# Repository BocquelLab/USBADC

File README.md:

# USBADC
Le USBADC est un petit PCB qui implémente plusieurs fonctionnalités:
+ Lecture de la tension de sortie du power meter
+ Lecture de la température ambiante
+ Communication USB pour interfacer avec un ordinateur
+ Génération de 28 volts 1 ampère à partir de 12 volts 3 Ampères pour l'amplificateur RF
+ Génération de 5 volts pour le power meter
+ Contrôlle de la vitesse du ventilateur pour évacuer la chaleur
+ 6 sorties open-drain pour pouvoir controller des appareils nécessitant de la puissance (`PB1`, `PB3`, `PB4`, `PB5`, `PB6`, `PB7`)
+ 6 sorties digitales 3.3 volts pour du contrôlle ne nécessitant pas de puissance (`PA3`, `PA4`, `PA5`, `PA6`, `PA7`, `PA8`)
+ LED de statut du PCB, `D2` clignote lorsque le micro-contrôlleur n'a pas d'erreurs, et 4 autres LEDs indiquent si les générateurs de tensions fonctionnent (3.3V, 5V, 12V, 28V)

## Hardware
KiCad 10.0 a été utilisé pour la conception du schématique et du PCB.

### Composantes

1. Entré 12V 3A
2. Sortie 28V 1A
3. Boost 12V -> 28V
4. Buck 12V -> 5V
5. Régulateur 5V -> 3.3V
6. Microcontrôlleur STM32U073K8U6
7. Connecteur USB A femelle
8. Connecteur SWD (Single Wire Debug)
9. Sorties open-drain et low power
10. Sortie PWM pour fan
11. Sortie pour alimentation du powermeter et entrée de la température
12. Entrée pour lecture de la puissance RF

### Programmation
Pour envoyer un programme sur le micro-contrôlleur, il y a le port USB ainsi qu'un port SWD près du connecteur USB (header 6 pins).
Pour le flasher par USB, il faut utiliser le périphérique DFU (Download Firmware Upgrade) qu'expose le bootloader to STM32. Par contre, je ne sais pas pourquoi, je n'ai pas été capable de le faire fonctionner plus qu'une seule fois.

Pour le flasher par SWD, il faut un STlink. J'ai utilisé un [STlink-V3MINIE](https://www.st.com/en/development-tools/stlink-v3minie.html) auquel j'avais accès, il serait peut-être pertinent de s'en acheter un. J'ai aussi utilisé [stlink-tools](https://github.com/stlink-org/stlink) pour envoyer le programme. Il faut brancher:

| stlink | PCB   |
|:------:|:-----:|
| VCC    | VDD1  |
| CLK    | SWCLK |
| GND    | GND   |
| TMS    | SWDIO |
| RST    | NRST  |

Le pinout du PCB est visible sur KiCad, l'ordre est VCC, SWCLK, GND, SWDIO, NRST, no-connect en partant de la pin extérieure.

### USB
La communication USB est faites avec un `STM32U073K8U6`, un micro-contrôlleur peu coûteux. C'est le moins cher qui a toutes les fonctionnalitées voulues, l'horloge pour le USB est générée à l'interne du chip.

### Génération 28V et 5V
Les bucks et boosts ont été générées avec l'outil [WEBENCH](https://webench.ti.com/power-designer/switching-regulator?powerSupply=0) de Texas Instrument pour être sûr que les circuits fonctionnent, jusqu'à maintenant, il n'y a eu aucuns problèmes.

### Sécurité
Pour la génération du 28V, il y a ~28 watts qui transitent dans cette partie du circuit. Il y a une fuse 4 ampères `F2` à l'entrée 12V du circuit et une fuse 1.5 ampères `F1` à la sortie 28V. De plus, il y a une diode schottky à la sortie 28V pour éviter d'envoyer des pics de tensions à l'amplificateur. Il y a aussi des condensateurs de capacitance équivalente 110µF pour lisser la tension entrante dans l'amplificateur.

Il y a des points de tests un peu partout sur le PCB pour être capable de débugger plus facilement si il arrive un problème.

### Boutons
Le PCB possède deux boutons, `BOOT0` et `Reset`.

`Reset` permet de redémarrer le microcontrôlleur, pratique pour débugger ou pour le redémarrer si il ne répond pas.

`BOOT0` permet de signaler au bootloader du microcontrôlleur que l'on désire flasher un programme pour qu'il expose la classe `DFU`. Il faut simplement tenir le bouton en appuyant sur `Reset`. Comme mentionné plus tôt, je ne comprends pas pourquoi je n'arrive pas à faire fonctionner cette option.

### Corrections à apporter sur une version future
Les connecteurs pour le ventilateur et le power meter overlap et ne peuvent donc pas être soudés directement sur le PCB.

Trouver pourquoi la programmation par DFU ne fonctionne pas et régler le problème.

Il m'est arrivé une fois que le board ne voulait pas démarrer, j'ai trouvé qu'il s'exposait comme périphérique DFU au démarage au lieu de CDC ACM et je n'étais pas capable de le faire booter plus loin que le bootloader. Je l'ai reflashé et ça a fonctionné, je n'ai pas revu ça depuis.

Mettre un connecteur USB mâle à la place d'un connecteur USB femelle car les connecteurs femelles sont réservés aux hôtes USB et les mâles aux périphériques.

Monitorer la tension du 28V avec le STM32 pour pouvoir voir son statut par USB au lieu de devoir regarder la LED. Sur la version actuelle, il est possible de mettre un diviseur de tension sur le pad 28V et rentrer ça dans la pin A3.

## Firmware
La grande majorité du code dans `firmware/` a été générée avec `STM32CubeMX`, un outil pour initialiser des projets pour des STM32, ils s'occupent d'initialiser toutes les périphériques, vérifier que la configuration de clocks choisie est correcte, etc.

Les paramètres pour CubeMX sont dans le fichier `firmware/USBADC.ioc`.

Le coeur de la logique a été implémentée dans `firmware/USBX/App/` en C.

### Compilation
Pour compiler le programme, il suffit d'écrire `make` si la toolchain de développement `arm` est installée. Je développais sur un ordinateur Linux et je roulais souvant 
```
make -j4; st-flash erase; st-flash write build/USBADC.bin 0x08000000
```
pour compiler et puis envoyer le programme sur le microcontrôlleur. Je ne suis pas certain que les `Makefile` sont supportés dans `STM32CubeIDE` (IDE de développement pour un STM32 installée sur l'ordinateur du laboratoire).

J'ai utilisé la "Arm GNU Toolchain 15.2.Rel1 (Build arm-15.86)) 15.2.1 20251203". Tout fonctionne avec celle là, il n'y a surement pas de soucis à prendre une autre version.

### Débuggage
Pour débugger, `STM32CubeIDE` et `stlink-tools` permettent d'ouvrir une session `gdb` et d'explorer la mémoire du microcontrolleur. Avec `stlink-tools`, je roulais dans un terminal `st-util` et dans l'autre `gdb build/USBADC.elf`, puis dans la session gdb `target remote localhost:4242`.

### Connection USB
Le périphérique USB crée expose une classe USB CDC ACM, (Character Device Class, Abstract Control Modem). Cette classe permet d'envoyer une série d'octet à l'appareil ainsi que d'en recevoir une. Lorsque branchée dans un ordinateur, le PCB devrait apparaître comme `/dev/ttyUSB*` sur Linux et `COM*` sur Windows. La LED devrait aussi clignotée si le microcontrôlleur est alimentée correctement et qu'il n'y a pas d'erreurs.

### Protocole de communication
La communication se produit par paquets entre le serveur (l'ordinateur) et le client (l'USBADC).
Un packet est une liste d'octets qui représente une commande ou une réponse. Le préfixe `0x` dénote de l'hexadécimale.

| Bytes       | Name        | Type      | Description                              |
|-------------|-------------|-----------|------------------------------------------|
| `0-3`       | Magic       | `u8[4]`   | `0xAA` `0x55` `0xAA` `0x55`              |
| `4-5`       | ID          | `u16`     | Request/response identifier.             |
| `6`         | Type        | `u8`      | Message type.                            |
| `7`         | Data Length | `u8`      | Bytes following this field.              |
| `8..7+N`    | Data        | `u8[]`    | Type-specific payload.                   |
| `8+N..11+N` | CRC         | `u32`     | Packet checksum using CRC32.             |

Le champs `Magic` permet d'identifier le début d'un paquet. `0xAA55AA55` a été choisi car c'est une séquence qui a peu de chance d'arriver avec du bruit ou dans des données, aussi, en binaire, les bits de 0xAA et 0x55 alternent et ça permet de reconnaitre à l'oeil le début de la séquence.

Le champs `ID` permet à l'USBADC de spécifier à quel paquet il répond en spécifiant l'ID du message qu'il a reçu dans sa réponse. Cela permet de répondre aux paquets dans un ordre différent de celui dans lequel ils ont été reçues si besoin.

Le champs `Type` est le type du message (ping, read_adc, write_pin, reboot, ...) et permet de spécifier comment interpréter les données,

Le champs `Data Length` est la longeur du champs `Data` en octets

Le champs `Data` est les données associées au `Type` choisi.

Le champs `CRC` (Cyclical Redundancy Checksum) sert à vérifier l'intégrité des données reçues. Lors de la réception d'un paquet, on calcule le checksum de tous les octets précédents. Si le checksum est identique à celui reçue, on peut être confiant qu'il n'y a pas eu d'erreur de transmission.

Le protocole est ses fonctions de sérialisation/désérialisation sont spécifiées dans `firmware/USBX/App/protocol.h` et `firmware/USBX/App/protocol.c`.
Les structures qui représentent les données transmises ont l'attribut `__attribute__((packed))` pour éviter les champs de "padding". Cet attribute garanti qu'il n'y en aura pas.

Sur le message `REQUEST_PING`, le client répond avec le message `RESPONSE_PONG` avec les mêmes données. Cela permet de s'assurer que le client fonctionne correctement.

Sur le message `REQUEST_READ_ADC`, le client répond avec `RESPONSE_READ_ADC` la tension lue sur le channel correspondant.

Sur le mesasge `REQUEST_WRITE_PIN`, le client répond avec `RESPONSE_STATUS` et sort l'état demandée sur la pin demandée.

Sur le mesasge `REQUEST_REBOOT`, le client répond avec `RESPONSE_STATUS` et redémarre (la communication sera coupée).

Sur le message `REQUEST_VERSION`, le client répond avec la version du protocole qu'il utilise. Cela permet de s'assurer que le client et le serveur sont sur la même version et que toutes les fonctionnalitées sont fonctionelles et supportées des deux côtés.

Sur tous les messages, le client peut répondre avec `RESPONSE_STATUS` et spécifier la raison (`enum USBADC_PROTOCOL_RESPONS_STATUS_REASONS`).

### Fichiers (`firmware/USBX/App/`)
+ `app_usbx_device.c`: Point d'entrée `ThreadX` qui initialise les tâches et le périphérique USB et les files.
+ `ux_device_cdc_acm.c`: Définitions de toutes les tâches concurrentes qui roulent, dont l'écriture et la lecture sur le canal USB, la lecture de l'ADC et le contrôle de la vitesse du ventilateur.
+ `byte_vector.c`: Définition des fonctions pour manipuler une liste d'octets qui ne peut pas être agrandie.
+ `protocol.c`: Définition des fonctions pour sérialiser/désérialiser les packets envoyées/reçues

## Software
Python 3.11 a été utilisé.

Dans `software/USBADC.py`, il y a la classe `USBADC` qui permet de communiquer avec le périphérique. Il est nécessaire d'installer `pyserial` pour être capable de communiquer.

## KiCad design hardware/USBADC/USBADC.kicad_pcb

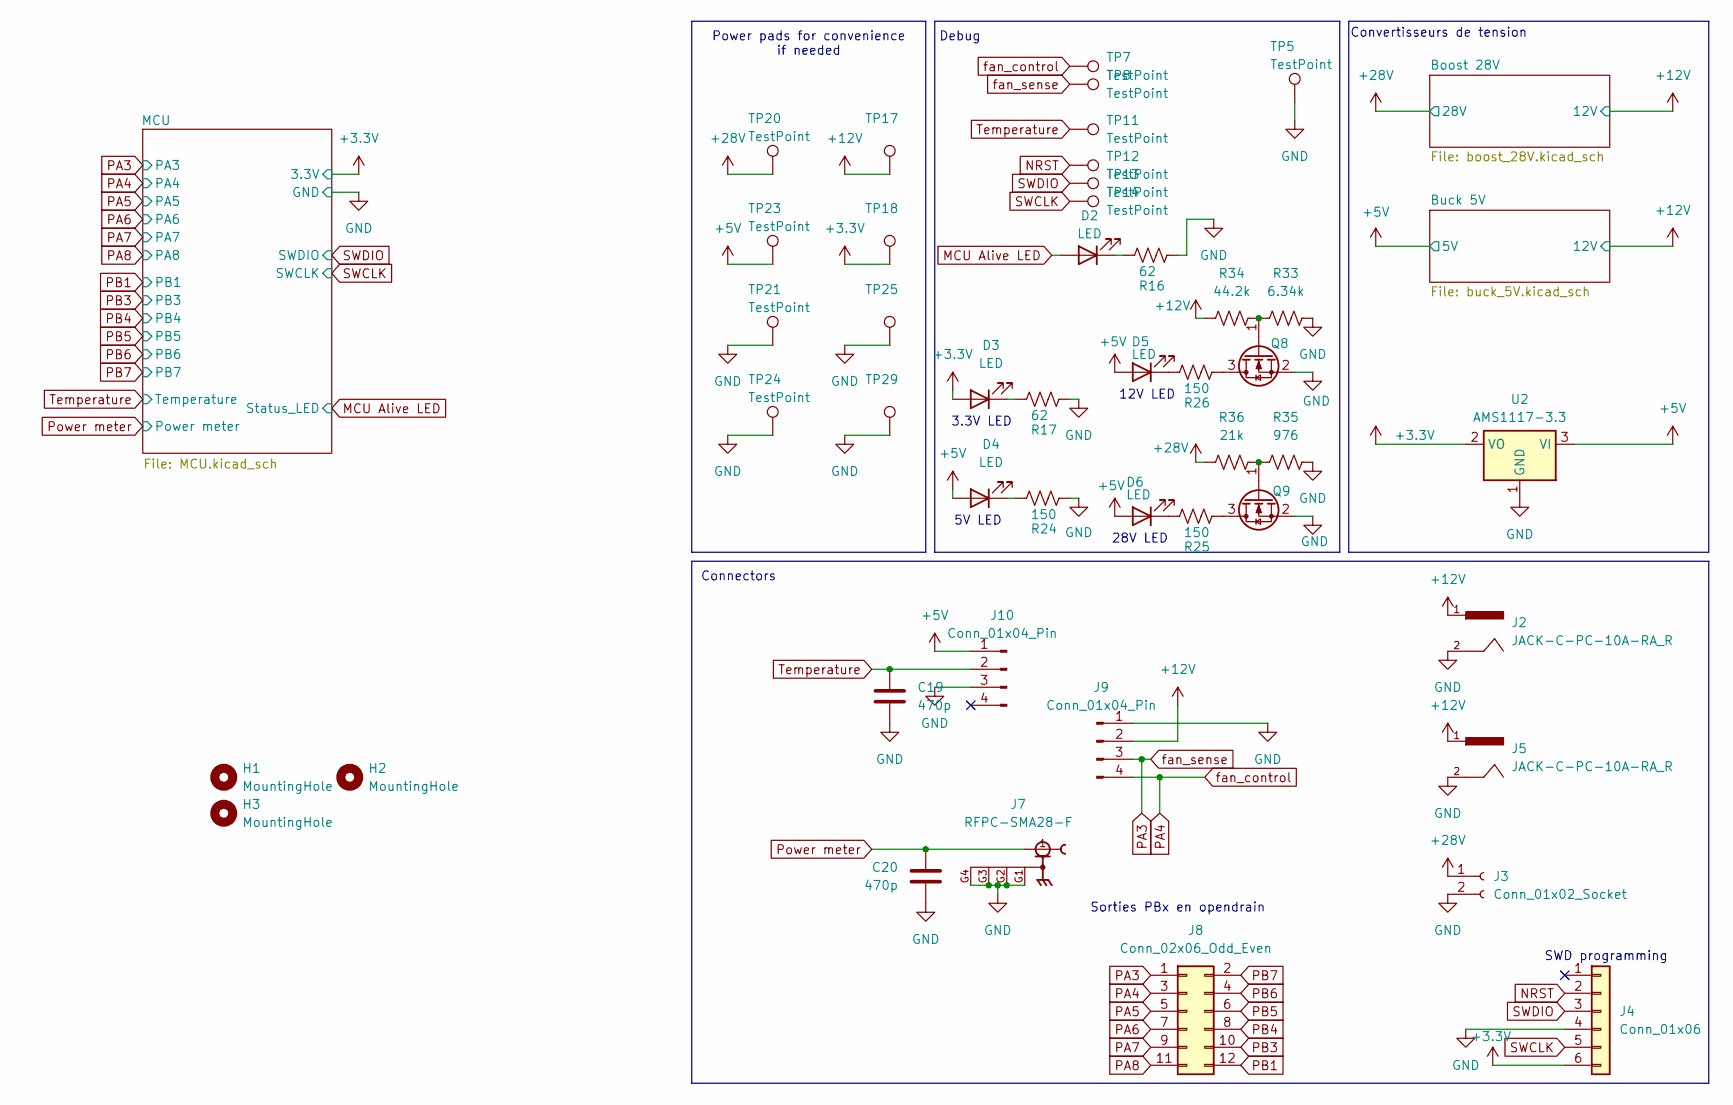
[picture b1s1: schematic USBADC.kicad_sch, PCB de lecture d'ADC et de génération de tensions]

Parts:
C19, C20: 470p; C_0603_1608Metric_Pad1.08x0.95mm_HandSolder
D2, D3, D4, D5, D6: LED; LED_0603_1608Metric_Pad1.05x0.95mm_HandSolder
H1, H2, H3: MountingHole; MountingHole_2.7mm_Pad_Via
J2, J5: JACK-C-PC-10A-RA_R; GLOBTECK_JACK-C-PC-10A-RA_R_; PARTREV A
J3: Conn_01x02_Socket; TerminalBlock_Phoenix_MKDS-1,5-2_1x02_P5.00mm_Horizontal
J4: Conn_01x06; PinHeader_1x06_P2.54mm_Vertical
J7: RFPC-SMA28-F; GRADCONN_RFPC-SMA28-F; PARTREV 1.0
J8: Conn_02x06_Odd_Even; PinSocket_2x06_P2.54mm_Horizontal
J9, J10: Conn_01x04_Pin; PinHeader_1x04_P2.54mm_Vertical
Q8, Q9: Q_NMOS_GSD; SOT-523
R16, R17: 62; R_0603_1608Metric_Pad0.98x0.95mm_HandSolder
R24, R25, R26: 150; R_0603_1608Metric_Pad0.98x0.95mm_HandSolder
R33: 6.34k; R_0603_1608Metric_Pad0.98x0.95mm_HandSolder
R34: 44.2k; R_0603_1608Metric_Pad0.98x0.95mm_HandSolder
R35: 976; R_0603_1608Metric_Pad0.98x0.95mm_HandSolder
R36: 21k; R_0603_1608Metric_Pad0.98x0.95mm_HandSolder
TP5, TP7, TP8, TP11, TP12, TP13, TP14: TestPoint; TestPoint_Pad_D1.5mm
TP17, TP18, TP20, TP21, TP23, TP24, TP25, TP29: TestPoint; TestPoint_Pad_3.0x3.0mm
U2: AMS1117-3.3; SOT-223-3_TabPin2

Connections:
+5V: D4.2 (A), D5.2 (A), D6.2 (A), J10.1, TP23.1 (1_1), U2.3 (VI); also elsewhere on the board
+12V: J2.1, J5.1, J9.2, R34.1, TP17.1 (1_1); also elsewhere on the board
+28V: J3.1, R36.1, TP20.1 (1_1); also elsewhere on the board
GND: C19.1, C20.1, J2.2, J3.2, J4.4, J5.2, J7.G1, J7.G2, J7.G3, J7.G4, J9.1, J10.3, Q8.2 (S), Q9.2 (S), R16.1, R17.1, R24.1, R33.1, R35.1, TP5.1 (1_1), TP21.1 (1_1), TP24.1 (1_1), TP25.1 (1_1), TP29.1 (1_1), U2.1 (GND); also elsewhere on the board
MCU Alive LED: D2.2 (A); also elsewhere on the board
NRST: J4.2, TP12.1 (1_1); also elsewhere on the board
unnamed: D2.1 (K), R16.2
unnamed: D3.1 (K), R17.2
unnamed: D4.1 (K), R24.2
unnamed: D5.1 (K), R26.2
unnamed: D6.1 (K), R25.2
unnamed: Q8.3 (D), R26.1
unnamed: Q8.1 (G), R33.2, R34.2
unnamed: Q9.3 (D), R25.1
unnamed: Q9.1 (G), R35.2, R36.2
PA3: J8.1, J9.3, TP8.1 (1_1); also elsewhere on the board
PA4: J8.3, J9.4, TP7.1 (1_1); also elsewhere on the board
PA5: J8.5; also elsewhere on the board
PA6: J8.7; also elsewhere on the board
PA7: J8.9; also elsewhere on the board
PA8: J8.11; also elsewhere on the board
PB1: J8.12; also elsewhere on the board
PB3: J8.10; also elsewhere on the board
PB4: J8.8; also elsewhere on the board
PB5: J8.6; also elsewhere on the board
PB6: J8.4; also elsewhere on the board
PB7: J8.2; also elsewhere on the board
Power meter: C20.2, J7.1; also elsewhere on the board
SWCLK: J4.5, TP14.1 (1_1); also elsewhere on the board
SWDIO: J4.3, TP13.1 (1_1); also elsewhere on the board
Temperature: C19.2, J10.2, TP11.1 (1_1); also elsewhere on the board
VDD1: D3.2 (A), J4.6, TP18.1 (1_1), U2.2 (VO); also elsewhere on the board

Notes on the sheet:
SWD programming
Convertisseurs de tension
28V LED
Connectors
Power pads for convenience if needed
12V LED
Debug
Sorties PBx en opendrain
3.3V LED
5V LED

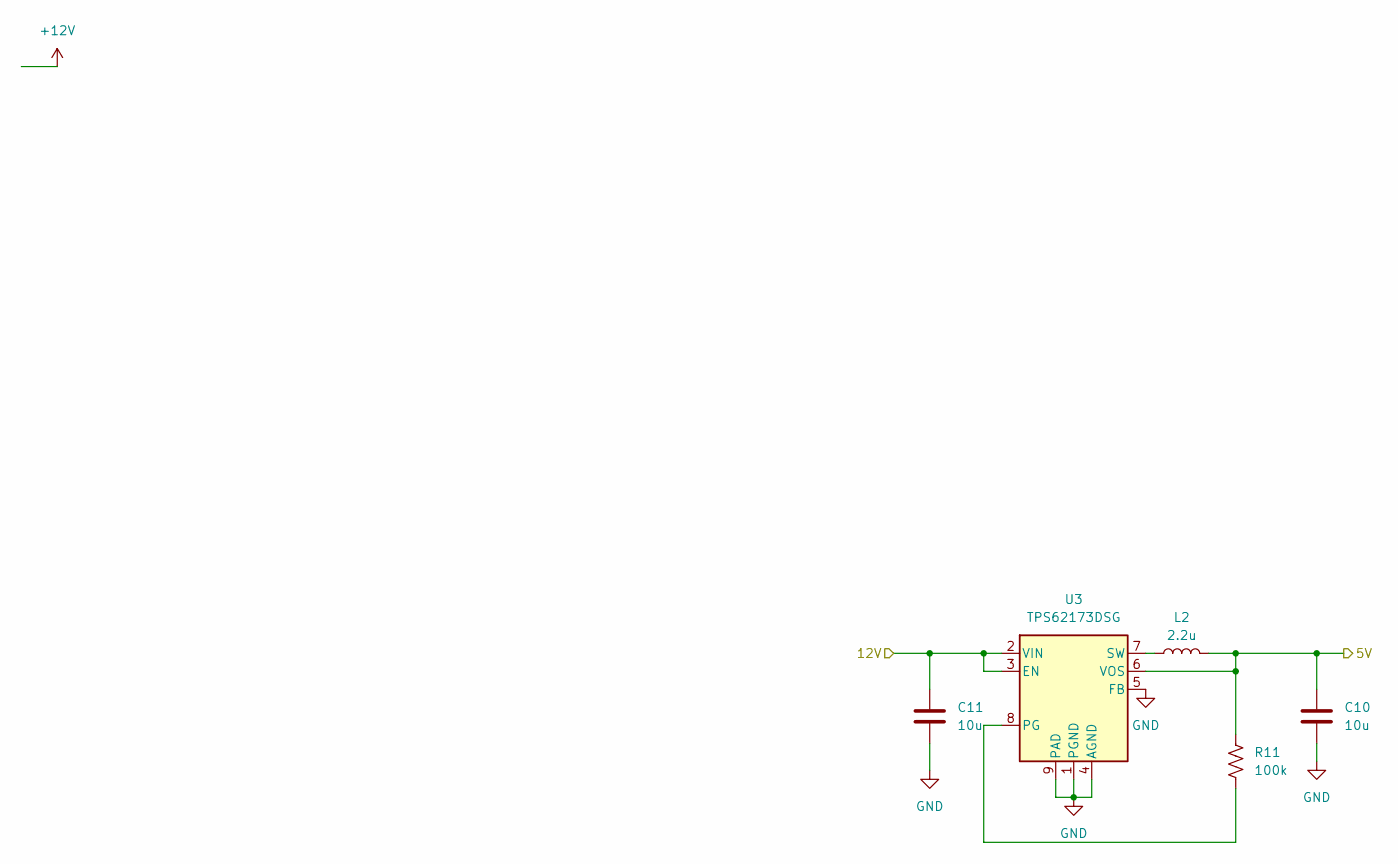
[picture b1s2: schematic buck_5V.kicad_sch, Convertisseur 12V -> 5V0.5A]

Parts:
C10, C11: 10u; C_0805_2012Metric_Pad1.18x1.45mm_HandSolder
L2: 2.2u; L_0603_1608Metric_Pad1.05x0.95mm_HandSolder
R11: 100k; R_0603_1608Metric_Pad0.98x0.95mm_HandSolder
U3: TPS62173DSG; WSON-8-1EP_2x2mm_P0.5mm_EP0.9x1.6mm_ThermalVias

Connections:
+5V: C10.1, L2.2, R11.1, U3.6 (VOS); also elsewhere on the board
+12V: C11.1, U3.2 (VIN), U3.3 (EN); also elsewhere on the board
GND: C10.2, C11.2, U3.1 (PGND), U3.4 (AGND), U3.5 (FB), U3.9 (PAD); also elsewhere on the board
unnamed: R11.2, U3.8 (PG)
unnamed: L2.1, U3.7 (SW)

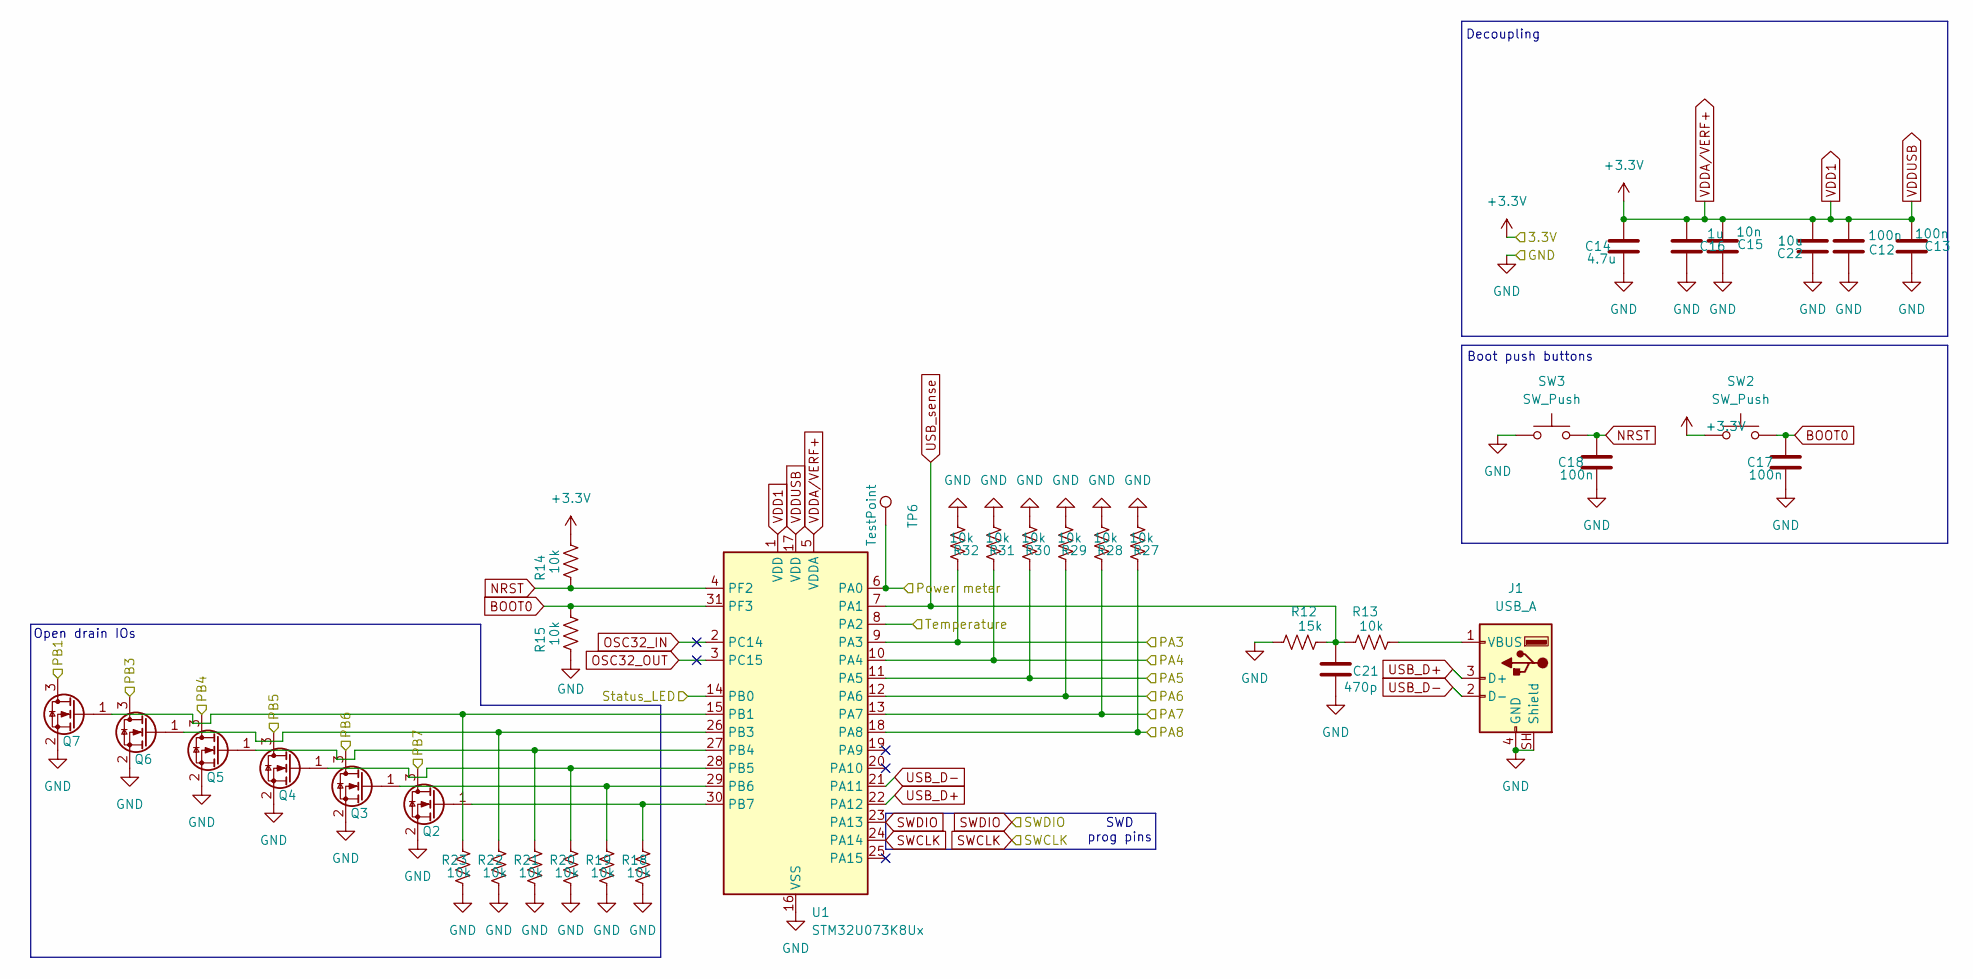
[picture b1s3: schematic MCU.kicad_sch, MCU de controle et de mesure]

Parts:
C12, C13, C17, C18: 100n; C_0603_1608Metric_Pad1.08x0.95mm_HandSolder
C14: 4.7u; C_0603_1608Metric_Pad1.08x0.95mm_HandSolder
C15: 10n; C_0603_1608Metric_Pad1.08x0.95mm_HandSolder
C16: 1u; C_0603_1608Metric_Pad1.08x0.95mm_HandSolder
C21: 470p; C_0603_1608Metric_Pad1.08x0.95mm_HandSolder
C22: 10u; C_0805_2012Metric_Pad1.18x1.45mm_HandSolder
J1: USB_A; USB_A_Molex_67643_Horizontal
Q2, Q3, Q4, Q5, Q6, Q7: Q_NMOS_GSD; SOT-523
R12: 15k; R_0603_1608Metric_Pad0.98x0.95mm_HandSolder
R13, R14, R15, R18, R19, R20, R21, R22, R23, R27, R28, R29, R30, R31, R32: 10k; R_0603_1608Metric_Pad0.98x0.95mm_HandSolder
SW2, SW3: SW_Push; SW_SPST_TL3305B
TP6: TestPoint; TestPoint_Pad_D1.5mm
U1: STM32U073K8Ux; QFN-32-1EP_5x5mm_P0.5mm_EP3.45x3.45mm

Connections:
BOOT0: C17.1, R15.2, SW2.2, U1.31 (PF3)
GND: C12.1, C13.1, C14.2, C15.1, C16.1, C17.2, C18.2, C21.1, C22.1, J1.4 (GND), J1.SH (Shield), Q2.2 (S), Q3.2 (S), Q4.2 (S), Q5.2 (S), Q6.2 (S), Q7.2 (S), R12.1, R15.1, R18.1, R19.1, R20.1, R21.1, R22.1, R23.1, R27.1, R28.1, R29.1, R30.1, R31.1, R32.1, SW3.1, U1.16 (VSS), U1.32 (VSS), U1.33 (VSS); also elsewhere on the board
MCU Alive LED: U1.14 (PB0); also elsewhere on the board
NRST: C18.1, R14.1, SW3.2, U1.4 (PF2); also elsewhere on the board
unnamed: J1.1 (VBUS), R13.2
unnamed: Q2.1 (G), R18.2, U1.30 (PB7)
unnamed: Q3.1 (G), R19.2, U1.29 (PB6)
unnamed: Q4.1 (G), R20.2, U1.28 (PB5)
unnamed: Q5.1 (G), R21.2, U1.27 (PB4)
unnamed: Q6.1 (G), R22.2, U1.26 (PB3)
unnamed: Q7.1 (G), R23.2, U1.15 (PB1)
OSC32_IN: U1.2 (PC14)
OSC32_OUT: U1.3 (PC15)
PA3: R32.2, U1.9 (PA3); also elsewhere on the board
PA4: R31.2, U1.10 (PA4); also elsewhere on the board
PA5: R30.2, U1.11 (PA5); also elsewhere on the board
PA6: R29.2, U1.12 (PA6); also elsewhere on the board
PA7: R28.2, U1.13 (PA7); also elsewhere on the board
PA8: R27.2, U1.18 (PA8); also elsewhere on the board
PB1: Q7.3 (D); also elsewhere on the board
PB3: Q6.3 (D); also elsewhere on the board
PB4: Q5.3 (D); also elsewhere on the board
PB5: Q4.3 (D); also elsewhere on the board
PB6: Q3.3 (D); also elsewhere on the board
PB7: Q2.3 (D); also elsewhere on the board
Power meter: TP6.1 (1_1), U1.6 (PA0); also elsewhere on the board
SWCLK: U1.24 (PA14); also elsewhere on the board
SWDIO: U1.23 (PA13); also elsewhere on the board
Temperature: U1.8 (PA2); also elsewhere on the board
USB_D+: J1.3 (D+), U1.22 (PA12)
USB_D-: J1.2 (D-), U1.21 (PA11)
USB_sense: C21.2, R12.2, R13.1, U1.7 (PA1)
VDD1: C12.2, C13.2, C14.1, C15.2, C16.2, C22.2, R14.2, SW2.1, U1.1 (VDD), U1.5 (VDDA), U1.17 (VDD); also elsewhere on the board

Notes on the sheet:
SWD prog pins
Open drain IOs
Boot push buttons
Decoupling

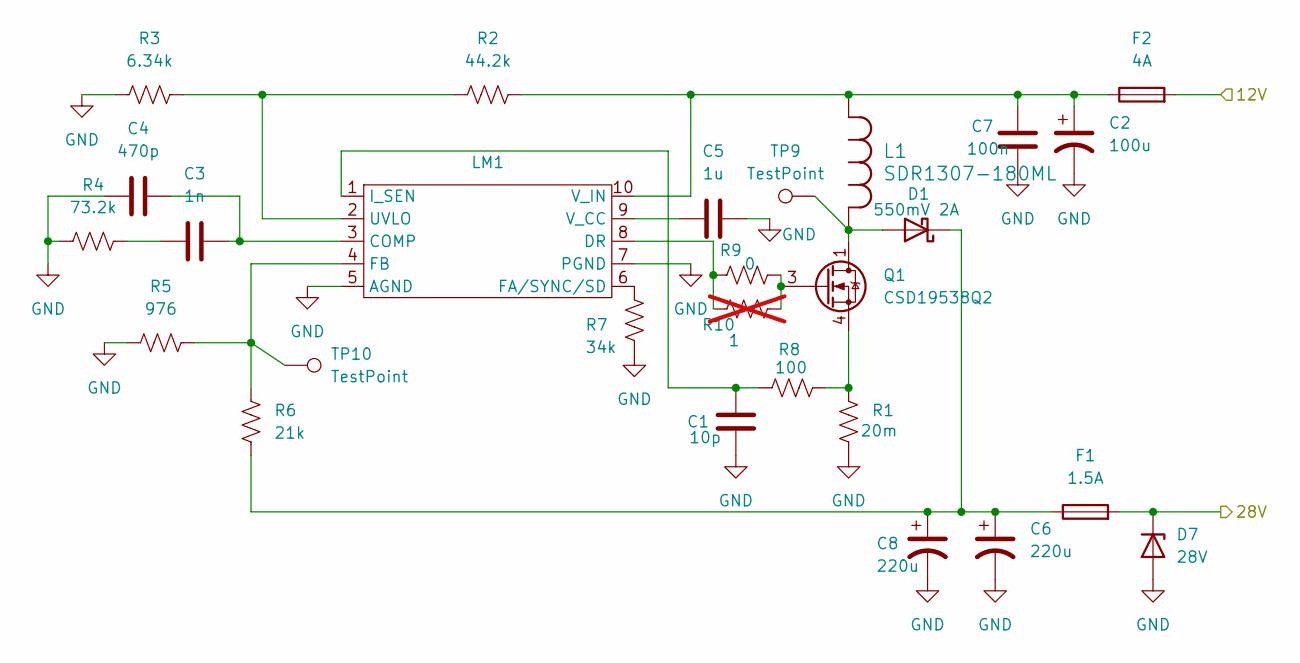
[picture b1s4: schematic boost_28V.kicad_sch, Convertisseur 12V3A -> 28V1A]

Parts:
C1: 10p; C_0603_1608Metric_Pad1.08x0.95mm_HandSolder
C2: 100u; CP_Elec_6.3x5.8
C3: 1n; C_0603_1608Metric_Pad1.08x0.95mm_HandSolder
C4: 470p; C_0603_1608Metric_Pad1.08x0.95mm_HandSolder
C5: 1u; C_0603_1608Metric_Pad1.08x0.95mm_HandSolder
C6, C8: 220u; CP_Elec_10x10
C7: 100n; C_0603_1608Metric_Pad1.08x0.95mm_HandSolder
D1: 550mV 2A; D_SOD-123F
D7: 28V; D_SMA_Handsoldering
F1: 1.5A; Fuse_1206_3216Metric_Pad1.42x1.75mm_HandSolder
F2: 4A; Fuse_1206_3216Metric_Pad1.42x1.75mm_HandSolder
L1: SDR1307-180ML; IND_BOURNS_SDR1307
LM1: TSSOP-10_3x3mm_P0.5mm
Q1: CSD19538Q2; Texas_DQK
R1: 20m; R_1206_3216Metric_Pad1.30x1.75mm_HandSolder
R2: 44.2k; R_0603_1608Metric_Pad0.98x0.95mm_HandSolder
R3: 6.34k; R_0603_1608Metric_Pad0.98x0.95mm_HandSolder
R4: 73.2k; R_0603_1608Metric_Pad0.98x0.95mm_HandSolder
R5: 976; R_0603_1608Metric_Pad0.98x0.95mm_HandSolder
R6: 21k; R_0603_1608Metric_Pad0.98x0.95mm_HandSolder
R7: 34k; R_0603_1608Metric_Pad0.98x0.95mm_HandSolder
R8: 100; R_0603_1608Metric_Pad0.98x0.95mm_HandSolder
R9: 0; SolderJumper-2_P1.3mm_Open_TrianglePad1.0x1.5mm
R10: 1; R_0603_1608Metric_Pad0.98x0.95mm_HandSolder; not fitted
TP9, TP10: TestPoint; TestPoint_Pad_D1.5mm

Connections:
+12V: F2.2; also elsewhere on the board
+28V: D7.1 (K), F1.2; also elsewhere on the board
GND: C1.2, C2.2, C4.1, C5.2, C6.2, C7.1, C8.2, D7.2 (A), LM1.5 (AGND), LM1.7 (PGND), R1.2, R3.2, R4.2, R5.2, R7.2; also elsewhere on the board
unnamed: C3.1, R4.1
unnamed: D1.2 (A), L1.1, Q1.1 (D), Q1.2 (D), Q1.5 (D), Q1.6 (D), Q1.8 (D), TP9.1 (1_1)
unnamed: C6.1, C8.1, D1.1 (K), F1.1, R6.2
unnamed: C3.2, C4.2, LM1.3 (COMP)
unnamed: LM1.8 (DR), R9.1, R10.1
unnamed: LM1.6 (FA/SYNC/SD), R7.1
unnamed: LM1.4 (FB), R5.1, R6.1, TP10.1 (1_1)
unnamed: C1.1, LM1.1 (I_SEN), R8.1
unnamed: LM1.2 (UVLO), R2.1, R3.1
unnamed: C5.1, LM1.9 (V_CC)
unnamed: C2.1, C7.2, F2.1, L1.2, LM1.10 (V_IN), R2.2
unnamed: Q1.3 (G), R9.2, R10.2
unnamed: Q1.4 (S), Q1.7 (S), R1.1, R8.2

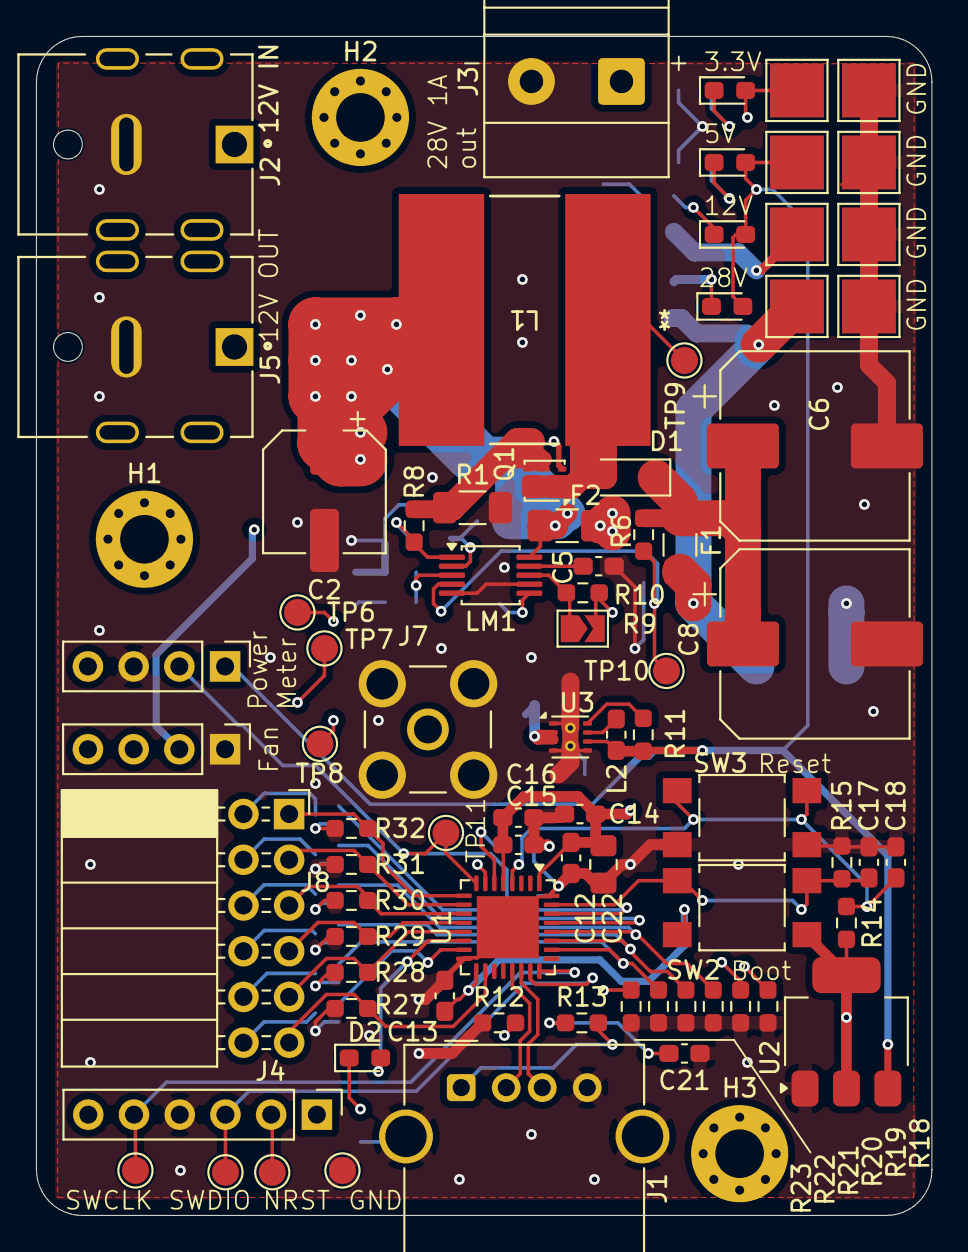
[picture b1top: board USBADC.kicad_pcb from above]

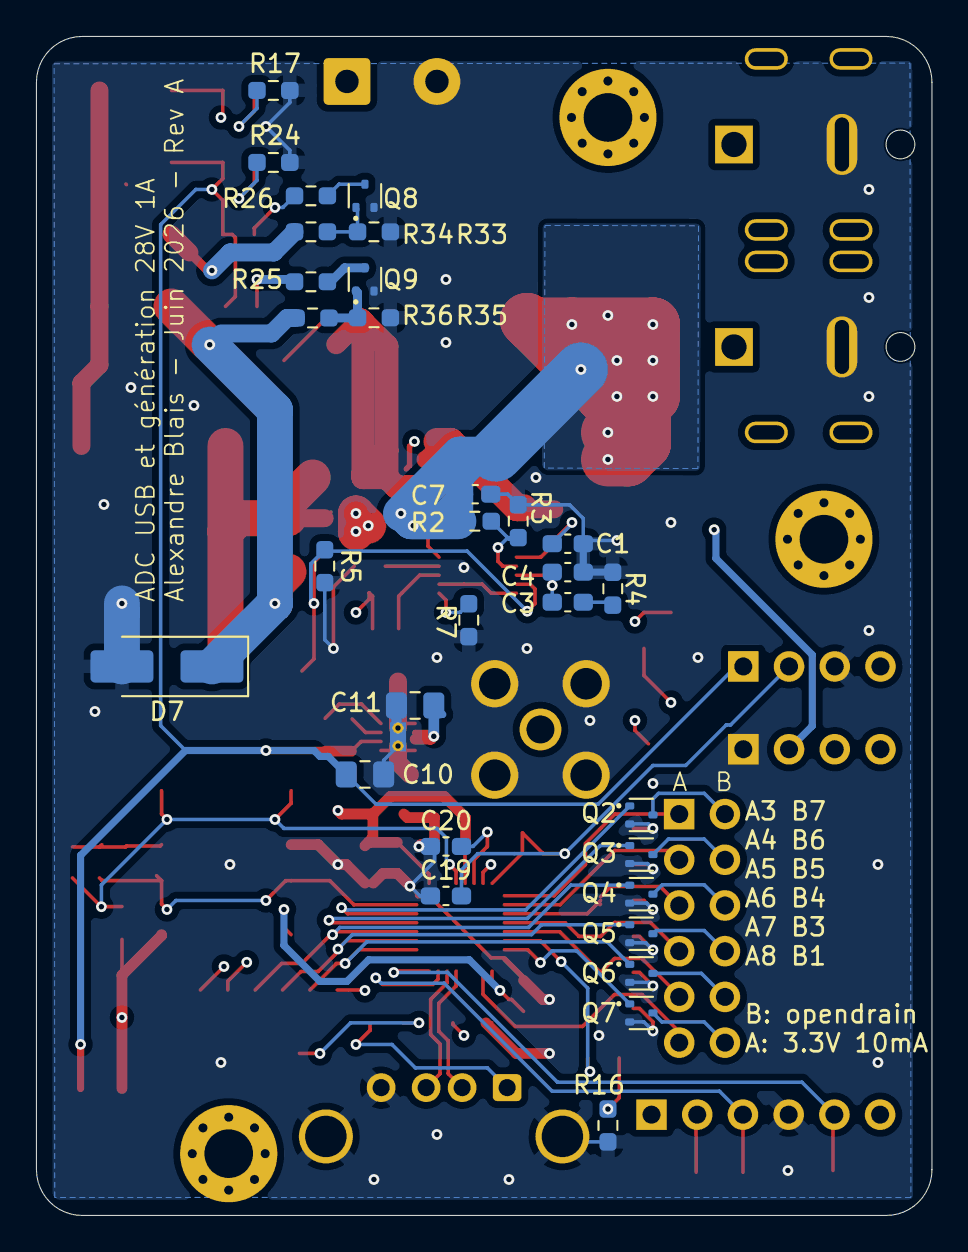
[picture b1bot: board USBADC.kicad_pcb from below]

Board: 4 copper layers, 49.8 x 65.5 mm, 113 parts (31 on the bottom side), 58 nets.

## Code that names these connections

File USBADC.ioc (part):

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Mcu.Name=STM32U073K8Ux
Mcu.Package=UFQFPN32
Mcu.UserName=STM32U073K8Ux
PA0-CK_IN.Mode=IN4
PA0-CK_IN.Signal=ADC1_IN4
PA1.Mode=IN5
PA1.Signal=ADC1_IN5
PA11\ [PA9].Mode=Device
PA11\ [PA9].Signal=USB_DM
PA12\ [PA10].Mode=Device
PA12\ [PA10].Signal=USB_DP
PA2.Mode=IN6
PA2.Signal=ADC1_IN6
PA3.Mode=IN7
PA3.Signal=ADC1_IN7
PA4.Signal=S_LPTIM2_CH1
PA5.Signal=GPIO_Output
PA6.Signal=GPIO_Output
PA7.Signal=GPIO_Output
PA8.Signal=GPIO_Output
PB0.Signal=GPIO_Output
PB1.Signal=GPIO_Output
PB3.Signal=GPIO_Output
PB4.Signal=GPIO_Output
PB5.Signal=GPIO_Output
PB6.Signal=GPIO_Output
PB7.Signal=GPIO_Output
RCC.HSE_VALUE=4000000
RCC.SYSCLKFreq_VALUE=16000000
board=custom
